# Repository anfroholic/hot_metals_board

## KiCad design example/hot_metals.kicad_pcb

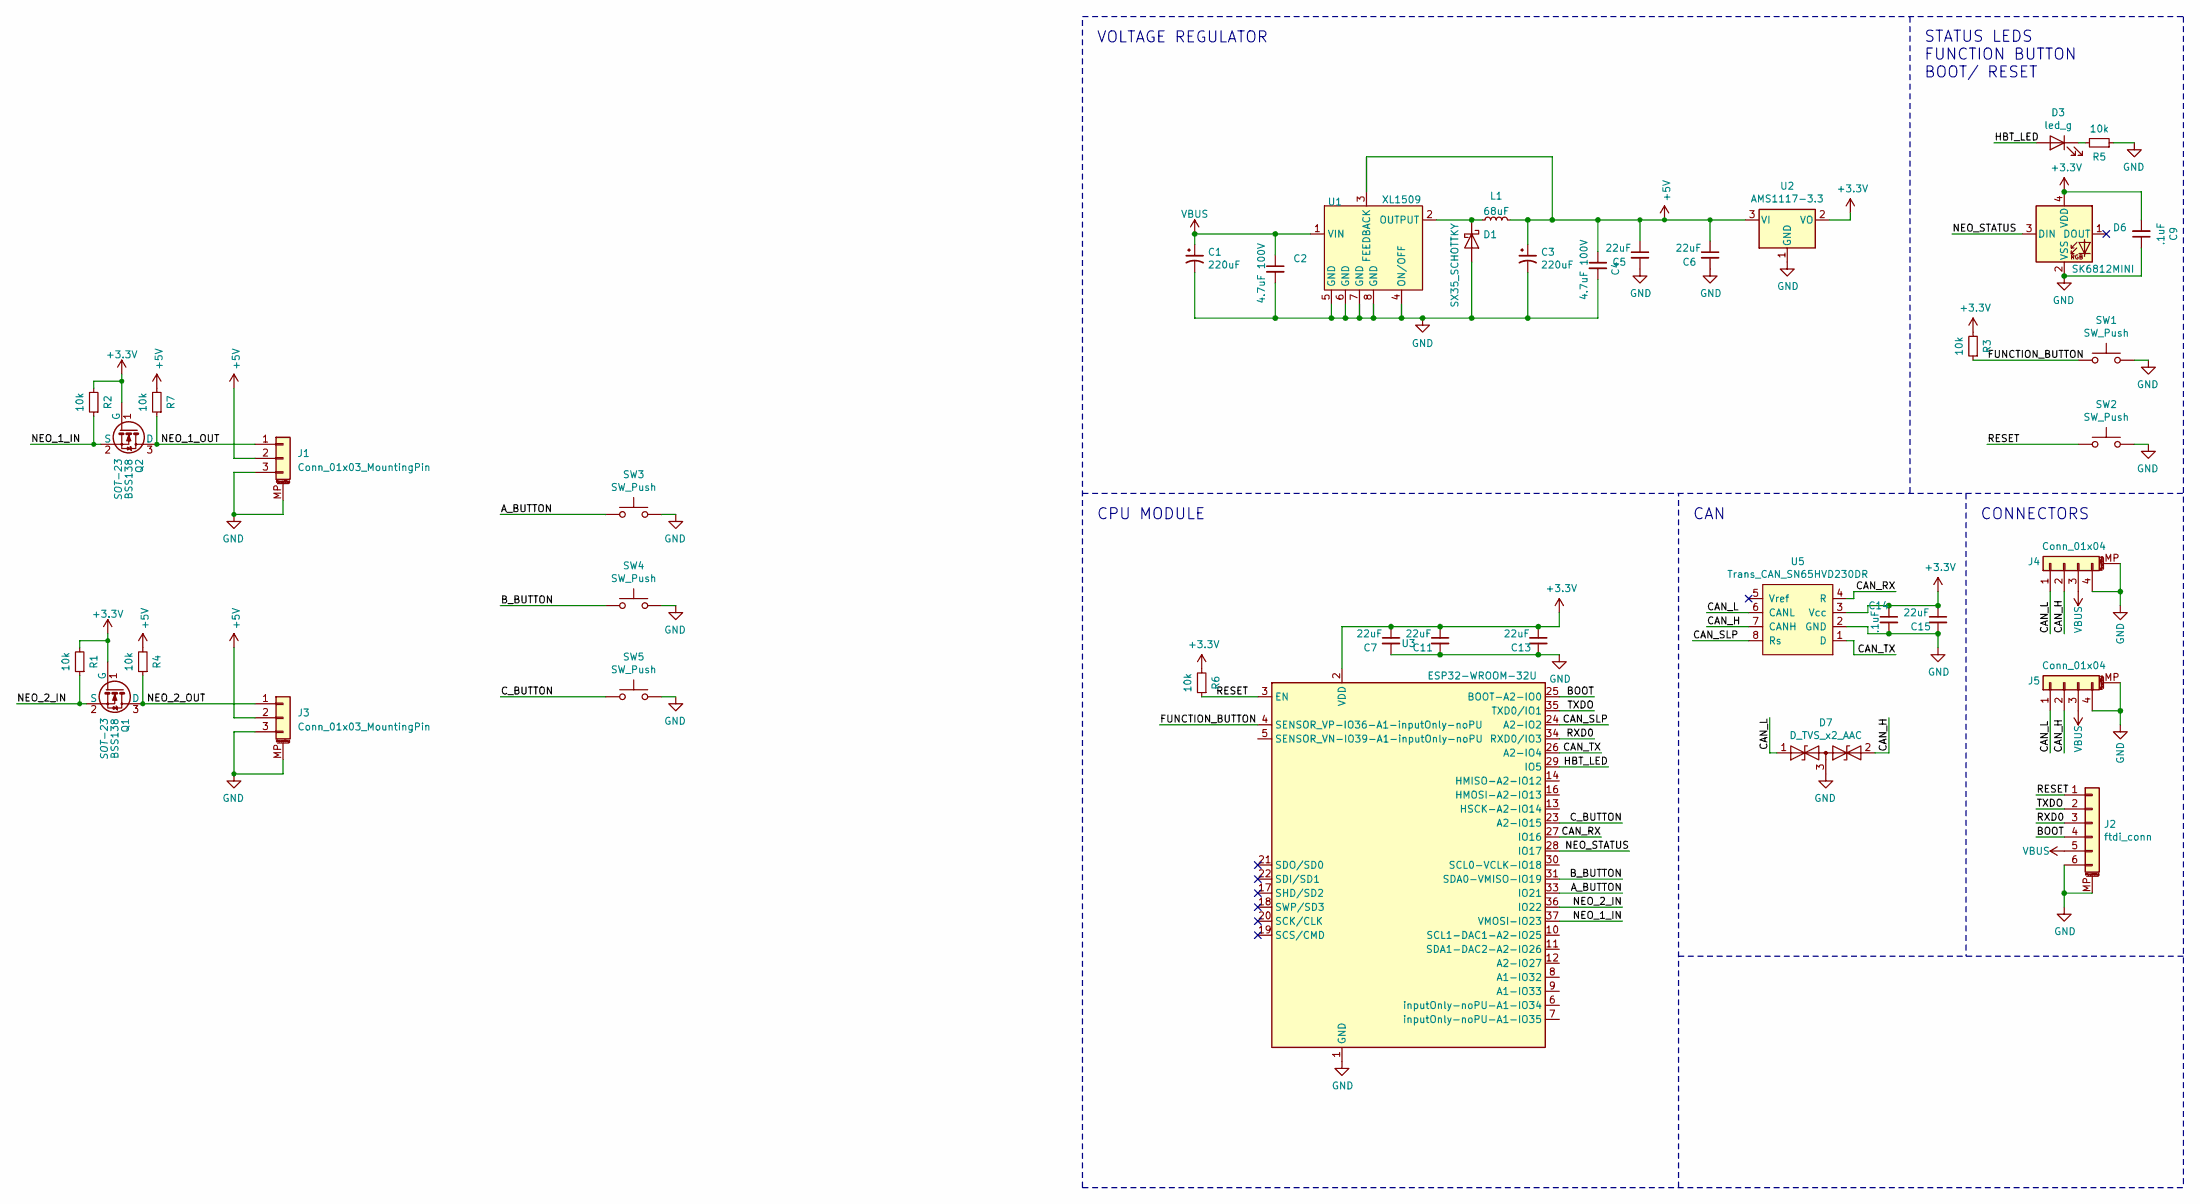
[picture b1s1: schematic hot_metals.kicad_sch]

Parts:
C1, C3: 220uF; CP_Elec_10x10.5
C2, C4: 4.7uF 100V; C_0805_2012Metric
C5, C6, C7, C11, C13, C15: 22uF; C_0805_2012Metric
C9, C14: .1uF; C_0603_1608Metric
D1: SX35_SCHOTTKY; D_SMA
D3: led_g; LED_0603_1608Metric
D6: SK6812MINI; LED_SK6812MINI_PLCC4_3.5x3.5mm_P1.75mm
D7: D_TVS_x2_AAC; SOT-23
J1, J3: Conn_01x03_MountingPin; CONN_JST_XH_3_VERTICAL
J2: ftdi_conn; JST_SH_BM06B-SRSS-TB_1x06-1MP_P1.00mm_Vertical
J4, J5: Conn_01x04; JST_PH_S4B-PH-SM4-TB_1x04-1MP_P2.00mm_Horizontal
L1: 68uF; INDUCTOR-68uH
Q1, Q2: BSS138; SOT-23
R1, R2, R3, R4, R5, R6, R7: 10k; R_0603_1608Metric
SW1, SW2, SW3, SW4, SW5: SW_Push; SWITCH_2x3_SMD_TACTILE_GREEN
U1: XL1509; SOIC-8_3.9x4.9mm_P1.27mm
U2: AMS1117-3.3; SOT-223-3_TabPin2
U3: ESP32-WROOM-32U; ESP32-WROOM-32U_evezor
U5: Trans_CAN_SN65HVD230DR; CAN-TRANS-SN65HVD230DR

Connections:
+3V3: C7.1, C9.2, C11.1, C13.1, C14.1, C15.1, D6.4 (VDD), Q1.1 (G), Q2.1 (G), R1.2, R2.2, R3.2, R6.2, U2.2 (VO), U3.2 (VDD), U5.3 (Vcc); also elsewhere on the board
+5V: C3.1, C4.1, C5.1, C6.1, J1.2, J3.2, L1.1, R4.2, R7.2, U1.3 (FEEDBACK), U2.3 (VI)
/A_BUTTON: SW3.1, U3.33 (IO21)
/BOOT: J2.4, U3.25 (BOOT-A2-IO0); also elsewhere on the board
/B_BUTTON: SW4.1, U3.31 (SDA0-VMISO-IO19)
/CAN_H: D7.2 (A2), J4.2, J5.2, U5.7 (CANH)
/CAN_L: D7.1 (A1), J4.1, J5.1, U5.6 (CANL); also elsewhere on the board
/CAN_RX: U3.27 (IO16), U5.4 (R)
/CAN_SLP: U3.24 (A2-IO2), U5.8 (Rs)
/CAN_TX: U3.26 (A2-IO4), U5.1 (D)
/C_BUTTON: SW5.1, U3.23 (A2-IO15)
/FUNCTION_BUTTON: R3.1, SW1.1, U3.4 (SENSOR_VP-IO36-A1-inputOnly-noPU)
/HBT_LED: D3.2 (A), U3.29 (IO5)
/NEO_1_IN: Q2.2 (S), R2.1, U3.37 (VMOSI-IO23)
/NEO_1_OUT: J1.1, Q2.3 (D), R7.1
/NEO_2_IN: Q1.2 (S), R1.1, U3.36 (IO22)
/NEO_2_OUT: J3.1, Q1.3 (D), R4.1
/NEO_STATUS: D6.3 (DIN), U3.28 (IO17)
/RESET: J2.1, R6.1, SW2.1, U3.3 (EN)
/RXD0: J2.3, U3.34 (RXD0/IO3)
/TXDO: J2.2, U3.35 (TXD0/IO1)
GND: C1.2, C2.2, C3.2, C4.2, C5.2, C6.2, C7.2, C9.1, C11.2, C13.2, C14.2, C15.2, D1.2 (A), D6.2 (VSS), D7.3 (common), J1.3, J1.MP (MountPin), J2.6, J2.MP (MountPin), J3.3, J3.MP (MountPin), J4.4, J4.MP (MountPin), J5.4, J5.MP (MountPin), R5.1, SW1.2, SW2.2, SW3.2, SW4.2, SW5.2, U1.4 (ON/OFF), U1.5 (GND), U1.6 (GND), U1.7 (GND), U1.8 (GND), U2.1 (GND), U3.1 (GND), U3.15 (GND), U3.38 (GND), U3.39 (GND), U5.2 (GND); also elsewhere on the board
unnamed: D1.1 (K), L1.2, U1.2 (OUTPUT)
unnamed: D3.1 (K), R5.2
VBUS: C1.1, C2.1, J2.5, J4.3, J5.3, U1.1 (VIN); also elsewhere on the board

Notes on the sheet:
VOLTAGE REGULATOR
CPU MODULE
CAN
STATUS LEDS FUNCTION BUTTON BOOT/ RESET
CONNECTORS

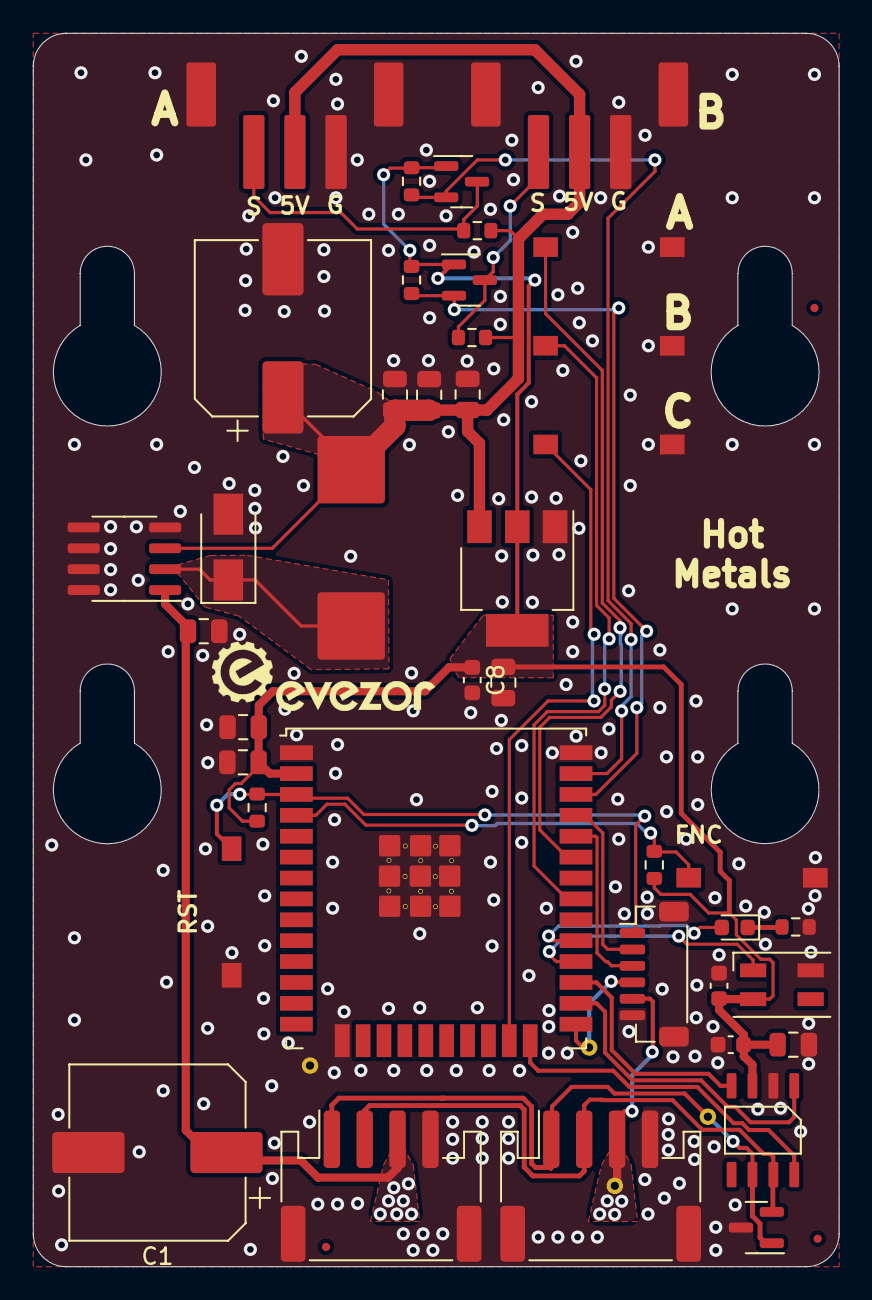
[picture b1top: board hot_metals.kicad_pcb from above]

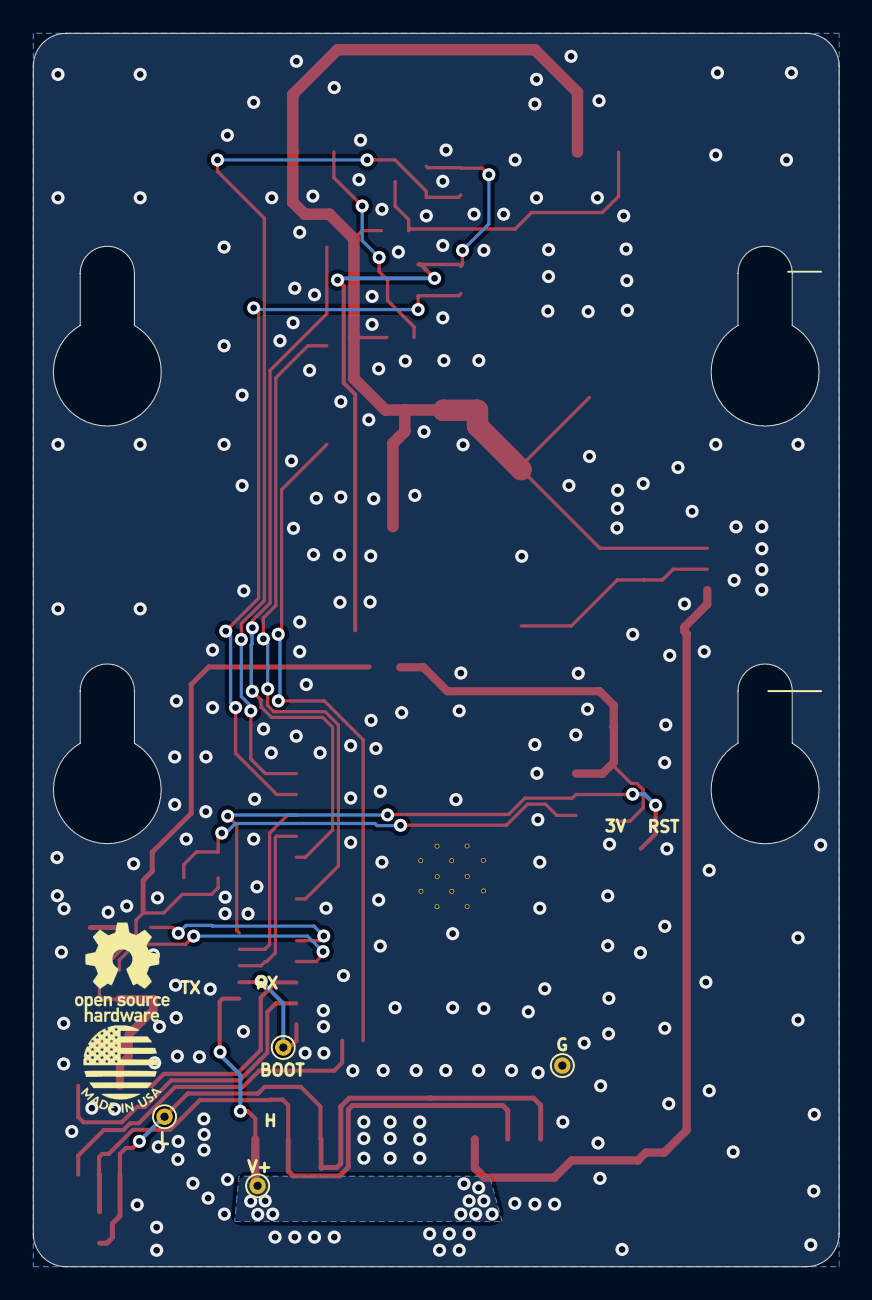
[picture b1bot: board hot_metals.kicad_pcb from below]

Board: 2 copper layers, 49.0 x 75.0 mm, 48 parts (4 on the bottom side), 25 nets.

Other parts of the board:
C8: .1uF; C_0603_1608Metric
FID1, FID2, FID3: Fiducial; Fiducial_0.5mm_Mask1mm
TP1, TP5, TP6, TP10: TestPoint; TestPoint_THTPad_D1.0mm_Drill0.5mm

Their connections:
+3V3: C8.1; also elsewhere on the board
/BOOT: TP6.1; also elsewhere on the board
/CAN_L: TP5.1; also elsewhere on the board
GND: C8.2, TP10.1; also elsewhere on the board
VBUS: TP1.1; also elsewhere on the board

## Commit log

2024-11-21 init
2024-11-21 move cad to example
